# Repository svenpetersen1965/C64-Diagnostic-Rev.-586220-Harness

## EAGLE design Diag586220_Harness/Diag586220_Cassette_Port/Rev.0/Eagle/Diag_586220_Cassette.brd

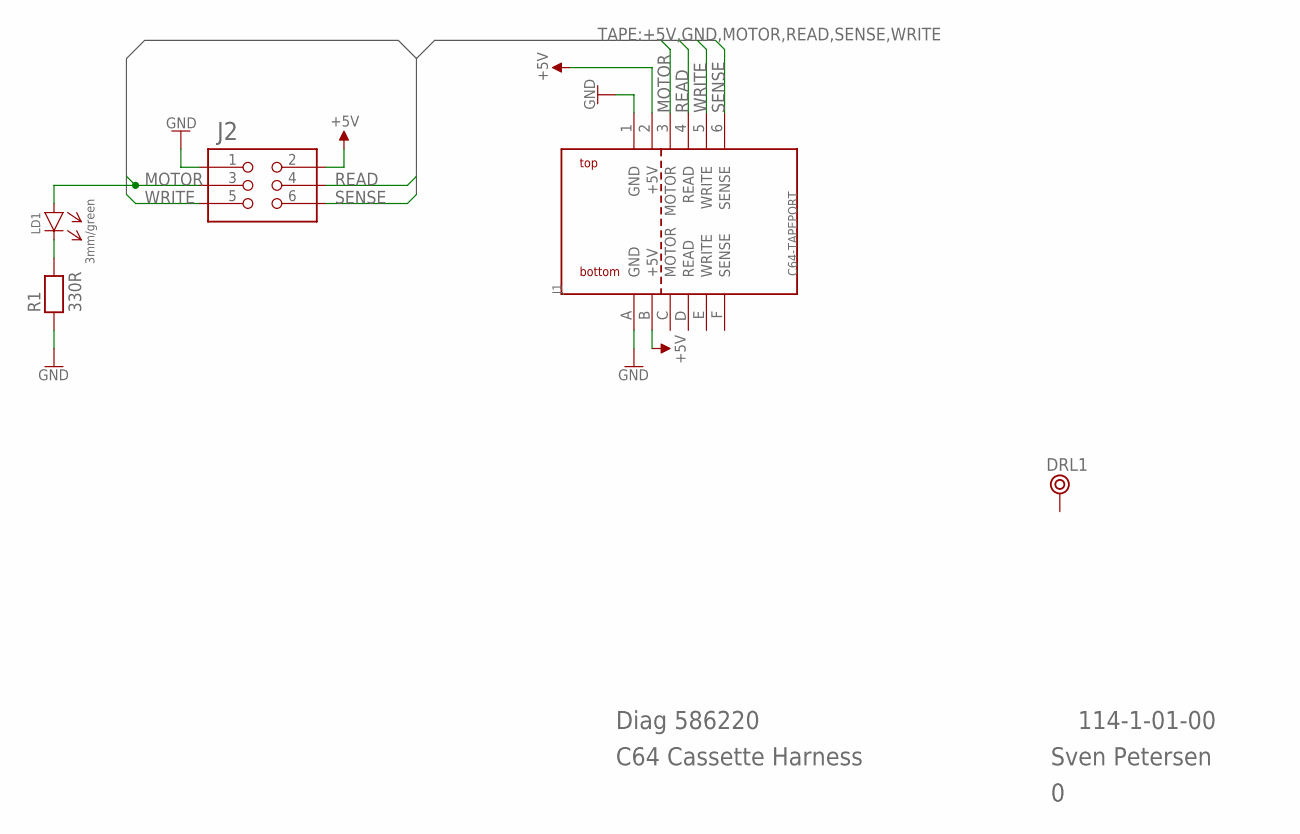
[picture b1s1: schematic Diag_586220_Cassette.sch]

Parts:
DRL1: BOHR3,5
J1: C64-TAPEPORT; TAPEPORT
J2: 2X03WV
LD1: 3mm/green; 3MM
R1: 330R; RS-2,5

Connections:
+5V: J1.2 (+5V), J1.B (+5V), J2.2
GND: J1.1 (GND), J1.A (GND), J2.1, R1.1
MOTOR: J1.3 (MOTOR), J2.3, LD1.A
unnamed: LD1.C (K), R1.2
READ: J1.4 (READ), J2.4
SENSE: J1.6 (SENSE), J2.6
WRITE: J1.5 (WRITE), J2.5

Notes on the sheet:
Diag 586220
C64 Cassette Harness
Sven Petersen
114-1-01-00

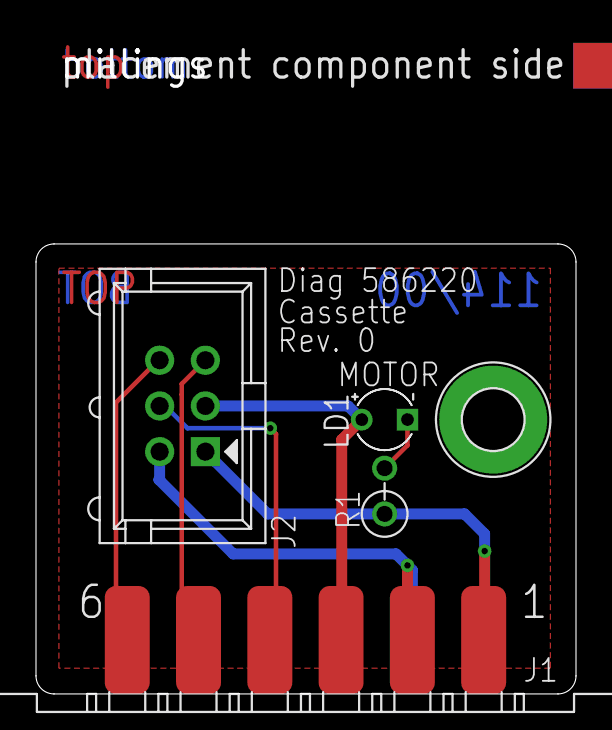
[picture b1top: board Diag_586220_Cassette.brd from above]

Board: 2 copper layers, 30.0 x 25.0 mm, 7 parts (0 on the bottom side), 7 nets.

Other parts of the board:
U$5: PCB-TITLE/
U$6: 2LAYER

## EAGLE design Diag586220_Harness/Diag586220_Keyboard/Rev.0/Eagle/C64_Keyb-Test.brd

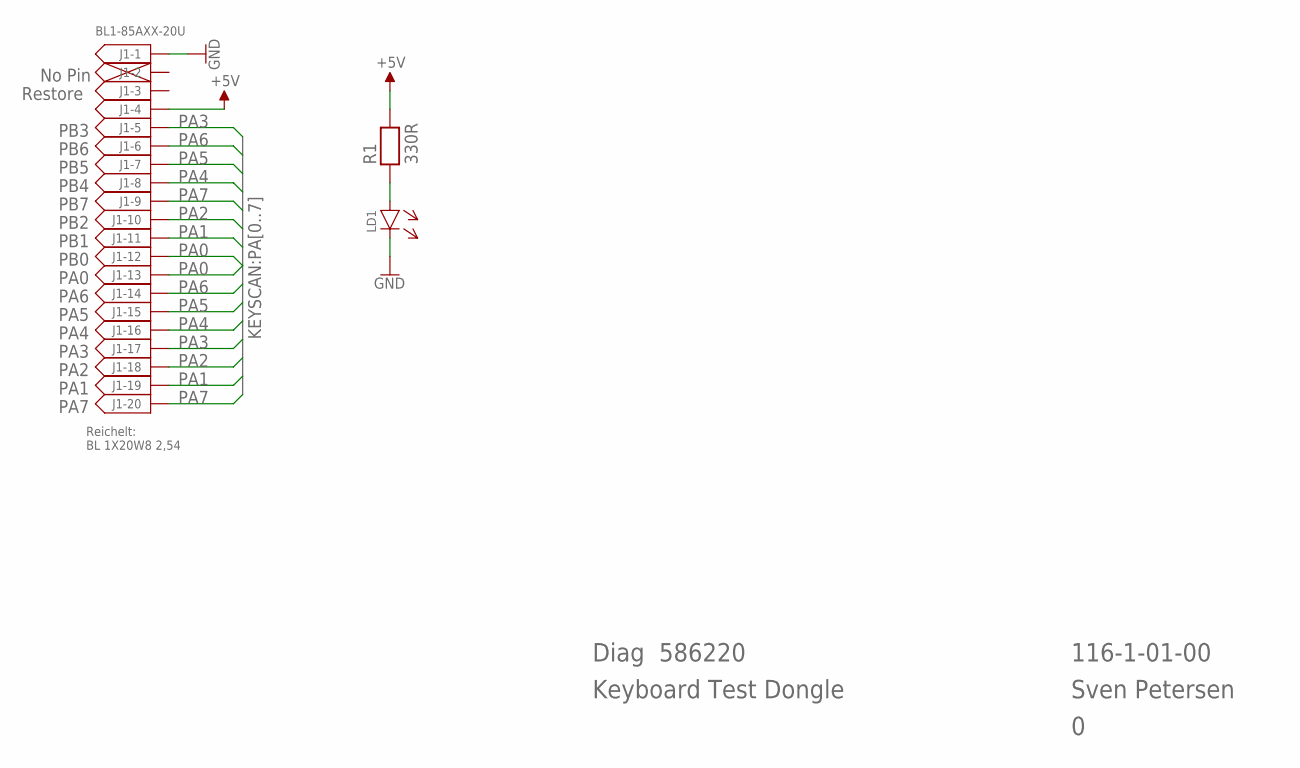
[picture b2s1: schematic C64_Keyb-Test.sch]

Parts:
J1: BL1-85AXX-20U
LD1: 3MM
R1: 330R; R-10

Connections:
+5V: J1.4, R1.2
GND: J1.1, LD1.C (K)
unnamed: LD1.A, R1.1
PA0: J1.12, J1.13
PA1: J1.11, J1.19
PA2: J1.10, J1.18
PA3: J1.5, J1.17
PA4: J1.8, J1.16
PA5: J1.7, J1.15
PA6: J1.6, J1.14
PA7: J1.9, J1.20

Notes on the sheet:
PB3
PB6
PB5
PB4
PB7
PB2
PB1
PB0
PA0
PA6
PA5
PA4
PA3
PA2
PA1
PA7
No Pin
Restore
Diag 586220
Keyboard Test Dongle
116-1-01-00
Sven Petersen
Reichelt: BL 1X20W8 2,54

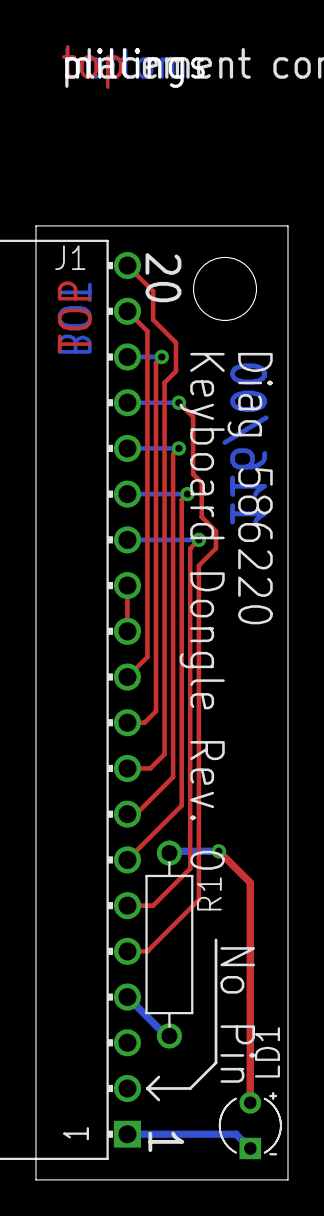
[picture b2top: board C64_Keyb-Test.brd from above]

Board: 2 copper layers, 14.0 x 53.0 mm, 5 parts (0 on the bottom side), 11 nets.

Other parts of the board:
U$6: 2LAYER
U$7: PCB-TITLE/

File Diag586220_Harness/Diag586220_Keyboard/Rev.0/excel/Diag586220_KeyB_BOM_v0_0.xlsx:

Diagnostic Rev. 586220 Harness - Keyboard Dongle Rev. 0
Bill of Material Rev. 0.0
Pos. | Qty | Value | Footprint | Ref.-No. | Comment
1 | 1 | 116-2-01-00 | 2 Layer | PCB Rev. 0 | 2 layer, Cu 35µ, HASL, 53.0mm x 14.0mm, 1.6mm FR4
2 | 1 | BL1-85AXX-20U | BL1-85AXX-20U | J1 | e.g. MPE Garry, Reichelt BL 1x20W8 2,54
3 | 1 | 3mm/green | 3MM | LD1 | LED
4 | 1 | 330R | R-10 | R1 | 1/4 Watt, 5%

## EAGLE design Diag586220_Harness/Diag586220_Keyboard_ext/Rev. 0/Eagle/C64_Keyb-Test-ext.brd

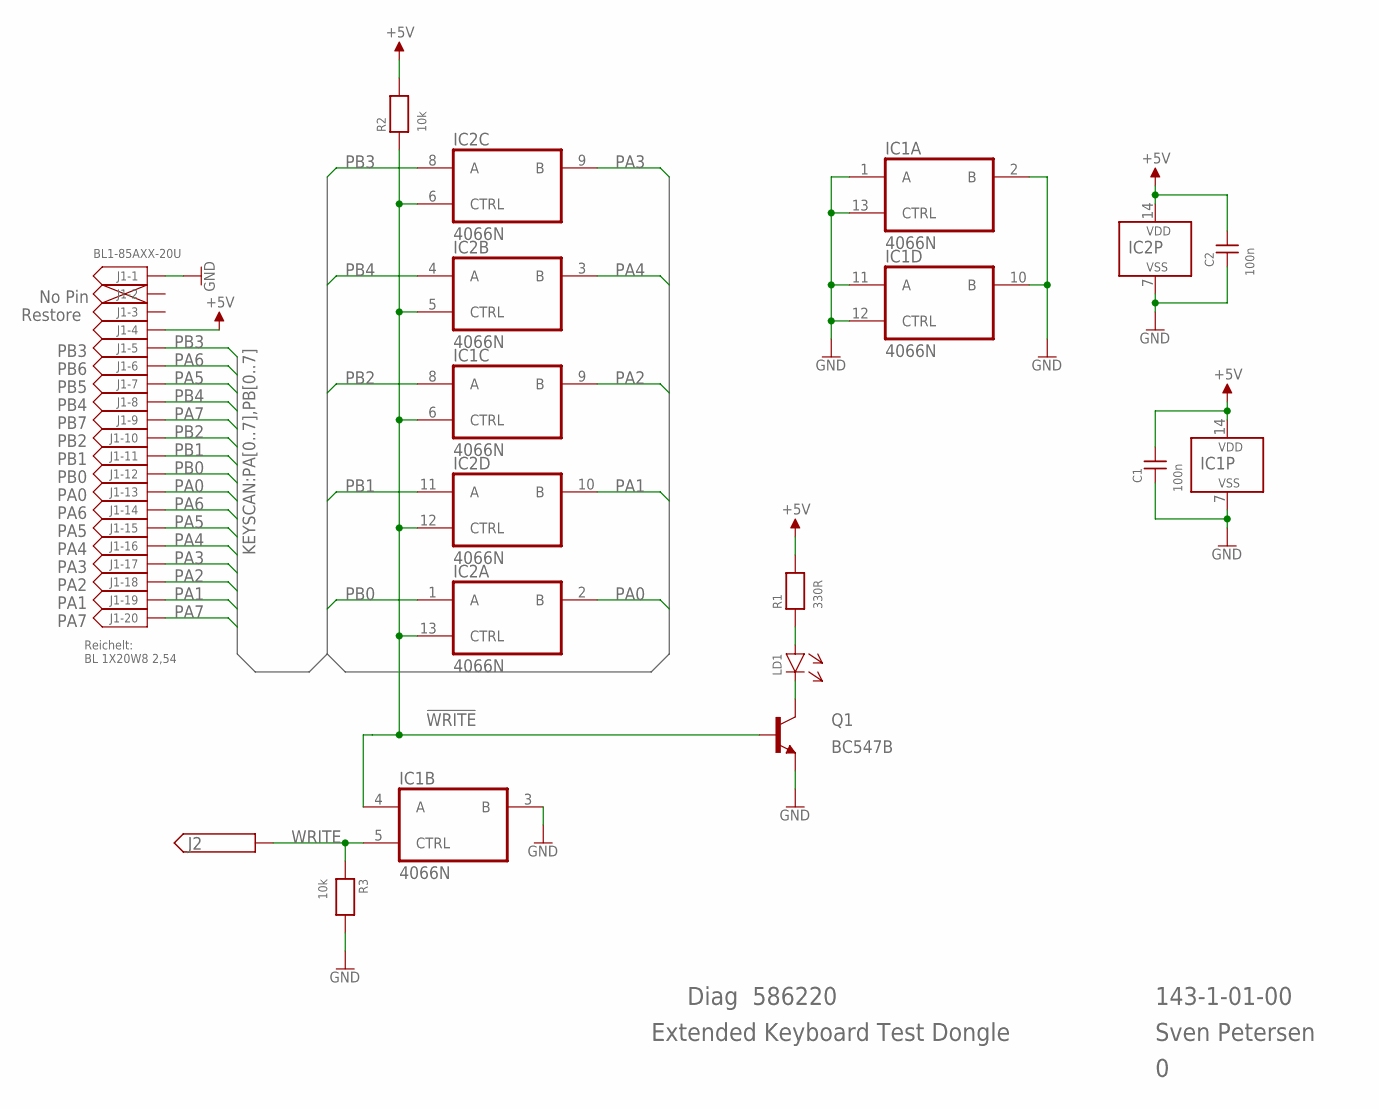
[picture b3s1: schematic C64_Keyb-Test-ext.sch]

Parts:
C1, C2: 100n; C-5
IC1, IC2: 4066N; DIL14
J1: BL1-85AXX-20U
J2: PINHD-1X1; 1X01
LD1: 3MM
Q1: BC547B; TO92
R1: 330R; R-10
R2, R3: 10k; R-10

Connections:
!WRITE: IC1.4 (A), IC1.6 (CTRL), IC2.5 (CTRL), IC2.6 (CTRL), IC2.12 (CTRL), IC2.13 (CTRL), Q1.2 (B), R2.1
+5V: C1.2, C2.2, IC1.14 (VDD), IC2.14 (VDD), J1.4, R1.2, R2.2
GND: C1.1, C2.1, IC1.1 (A), IC1.2 (B), IC1.3 (B), IC1.7 (VSS), IC1.10 (B), IC1.11 (A), IC1.12 (CTRL), IC1.13 (CTRL), IC2.7 (VSS), J1.1, Q1.1 (E), R3.2
unnamed: LD1.A, R1.1
unnamed: LD1.C (K), Q1.3 (C)
PA0: IC2.2 (B), J1.13
PA1: IC2.10 (B), J1.19
PA2: IC1.9 (B), J1.18
PA3: IC2.9 (B), J1.17
PA4: IC2.3 (B), J1.16
PA5: J1.7, J1.15
PA6: J1.6, J1.14
PA7: J1.9, J1.20
PB0: IC2.1 (A), J1.12
PB1: IC2.11 (A), J1.11
PB2: IC1.8 (A), J1.10
PB3: IC2.8 (A), J1.5
PB4: IC2.4 (A), J1.8
WRITE: IC1.5 (CTRL), J2.1, R3.1

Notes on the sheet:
PB3
PB6
PB5
PB4
PB7
PB2
PB1
PB0
PA0
PA6
PA5
PA4
PA3
PA2
PA1
PA7
No Pin
Restore
Diag 586220
Extended Keyboard Test Dongle
143-1-01-00
Sven Petersen
Reichelt: BL 1X20W8 2,54

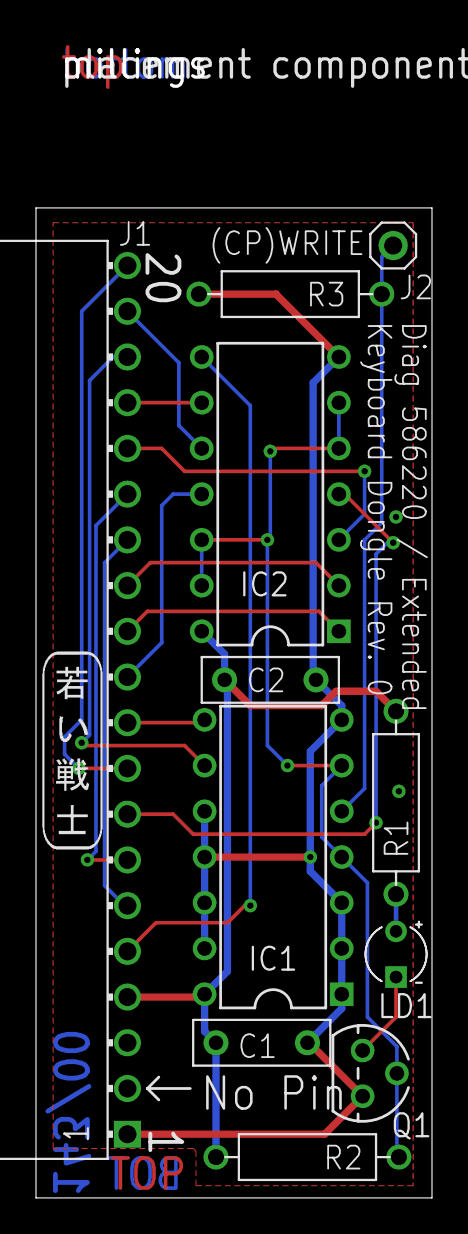
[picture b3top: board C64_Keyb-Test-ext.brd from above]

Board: 2 copper layers, 22.0 x 55.0 mm, 14 parts (0 on the bottom side), 19 nets.

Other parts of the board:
U$6: 2LAYER
U$7: PCB-TITLE/
U$17: SVEN_TAG

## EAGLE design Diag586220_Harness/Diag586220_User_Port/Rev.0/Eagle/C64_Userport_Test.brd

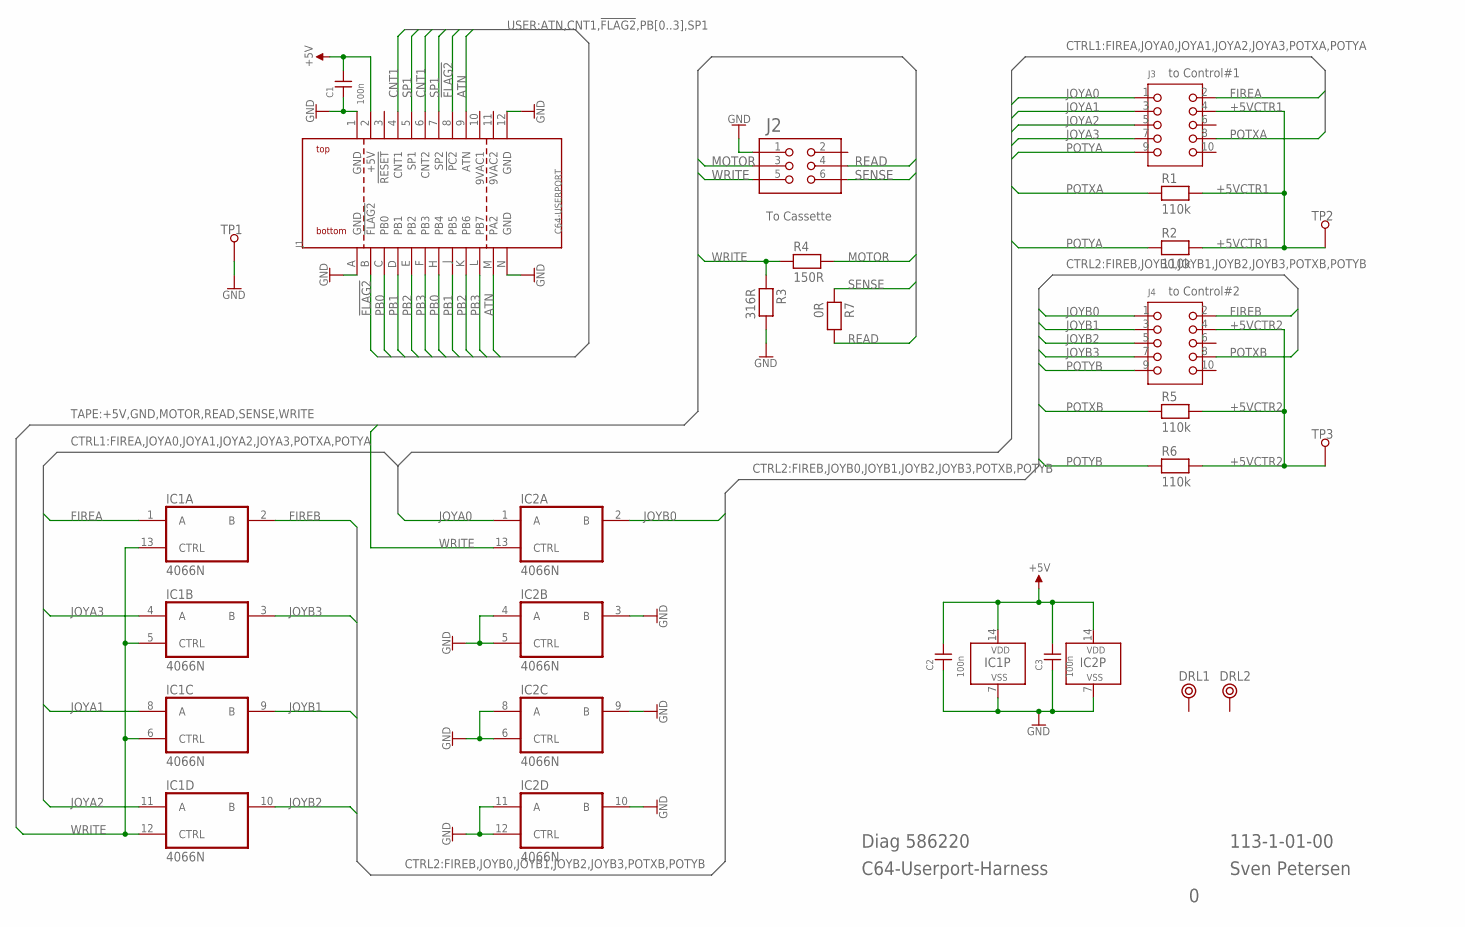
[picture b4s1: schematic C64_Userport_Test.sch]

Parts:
C1, C2, C3: 100n; C-2,5
DRL1, DRL2: BOHR3,2
IC1, IC2: 4066N; DIL14
J1: C64-USERPORT; USERPORT
J2: 2X03WV
J3, J4: 2X05WV
R1, R2, R5, R6: 110k; R-10
R3: 316R; R-10
R4: 150R; R-10
R7: 0R; R-10
TP1, TP2, TP3: L1,2_R; 1,2MM_R

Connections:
9VAC1: J1.10 (9VAC1)
9VAC2: J1.11 (9VAC2)
!FLAG2: J1.8 (!PC2), J1.B (!FLAG2)
+5V: C1.2, C2.2, C3.2, IC1.14 (VDD), IC2.14 (VDD), J1.2 (+5V)
+5VCTR1: J3.4, R1.2, R2.2, TP2.1
+5VCTR2: J4.4, R5.2, R6.2, TP3.1
ATN: J1.9 (ATN), J1.M (PA2)
CNT1: J1.4 (CNT1), J1.6 (CNT2)
FIREA: IC1.1 (A), J3.2
FIREB: IC1.2 (B), J4.2
GND: C1.1, C2.1, C3.1, IC1.7 (VSS), IC2.3 (B), IC2.4 (A), IC2.5 (CTRL), IC2.6 (CTRL), IC2.7 (VSS), IC2.8 (A), IC2.9 (B), IC2.10 (B), IC2.11 (A), IC2.12 (CTRL), J1.1 (GND), J1.12 (GND), J1.A (GND), J1.N (GND), J2.1, R3.2, TP1.1
JOYA0: IC2.1 (A), J3.1
JOYA1: IC1.8 (A), J3.3
JOYA2: IC1.11 (A), J3.5
JOYA3: IC1.4 (A), J3.7
JOYB0: IC2.2 (B), J4.1
JOYB1: IC1.9 (B), J4.3
JOYB2: IC1.10 (B), J4.5
JOYB3: IC1.3 (B), J4.7
MOTOR: J2.3, R4.2
PB0: J1.C (PB0), J1.H (PB4)
PB1: J1.D (PB1), J1.J (PB5)
PB2: J1.E (PB2), J1.K (PB6)
PB3: J1.F (PB3), J1.L (PB7)
POTXA: J3.8, R1.1
POTXB: J4.8, R5.1
POTYA: J3.9, R2.1
POTYB: J4.9, R6.1
READ: J2.4, R7.2
SENSE: J2.6, R7.1
SP1: J1.5 (SP1), J1.7 (SP2)
WRITE: IC1.5 (CTRL), IC1.6 (CTRL), IC1.12 (CTRL), IC1.13 (CTRL), IC2.13 (CTRL), J2.5, R3.1, R4.1

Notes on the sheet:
Diag 586220
C64-Userport-Harness
Sven Petersen
To Cassette
to Control#1
to Control#2
113-1-01-00

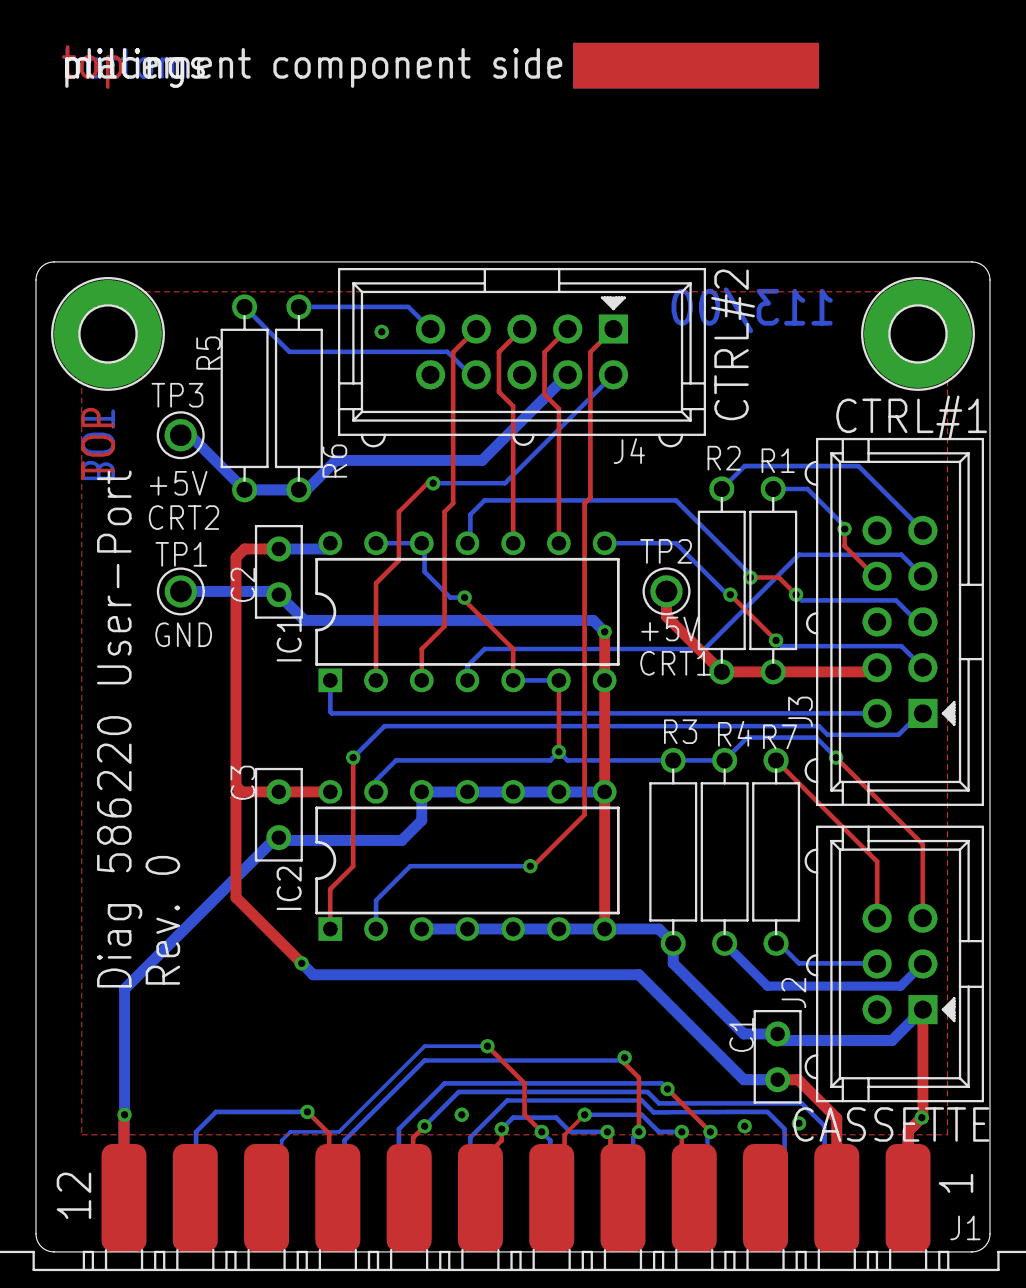
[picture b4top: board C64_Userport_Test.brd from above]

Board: 2 copper layers, 53.0 x 55.0 mm, 23 parts (0 on the bottom side), 30 nets.

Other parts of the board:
U$17: 2LAYER
U$18: PCB-TITLE/

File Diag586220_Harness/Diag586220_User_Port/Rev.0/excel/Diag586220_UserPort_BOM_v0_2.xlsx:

Diagnostic Rev. 586220 Harness - User Port Rev. 0
Bill of Material Rev. 0.2
Pos. | Qty | Value | Footprint | Ref.-No. | Comment
1 | 1 | 113-2-01-00 | 2 Layer | PCB Rev. 0 | 2 layer, Cu 35µ, HASL, LLL x BBB, 1.6mm FR4
2 | 1 | 2x3 box connector | 2X03WV | J2 | e.g. Reichelt WSL 6G
3 | 2 | 2x5 box connector | 2X05WV | J3, J4 | e.g. Reichelt WSL 10G
4 | 1 | 0R | R-10 | R7 | 0 Ohm bridge
5 | 3 | 100n/50V | C-2,5 | C1, C2, C3 | cer. cap, 2.5mm pitch
6 | 4 | 110k | R-10 | R1, R2, R5, R6 | 1/4W, 1%
7 | 1 | 150R | R-10 | R4 | 1/4W, 5%
8 | 1 | 316R | R-10 | R3 | 1/4W, 5% (316W works, 330W should work as well)
9 | 2 | HCF4066B | DIL14 | IC1, IC2 | ST Micro or equivalent
10 | 2 | DIL 14 | DIL14 | (IC1), (IC2) | DIL IC sockets
11 | 1 | 2x12, 3.96mm pitch | USERPORT | J1 | edge connector, C64 user port
12 | 3 | TP 1pin | 1,2MM_R | TP1, TP2, TP3 | Pin Header, e.g. Reichelt RND 205-00622
13 | 127cm | 10p/AWG28/1,27mm |  | Doc-No. 113-3-02-00 & Doc.-No. 113-2-01-00 | Ribbon Cable
14 | 2 | 6p IDC receptable, 2,54mm |  | Doc.-No. 113-2-01-00 | e.g. Reichelt RND 205-00680
15 | 2 | 10p IDC receptable, 2,54mm |  | Doc.-No. 113-2-02-00 | e.g. Reichelt RND 205-00682
16 | 2 | 9p D-SUB (female), IDC |  | Doc.-No. 113-2-02-00 | e.g. Reichelt D-SUB BU 09FB
17 | 1 | DIN-plug 6p |  | Doc.-No. 113-2-03-00 | e.g. Reichelt MAS 60
18 | 4cm | Wire 0,25mm², red |  | Doc.-No. 113-2-03-00 | wire, color what ever
 |  | Rev. 0.1 ® 0.2
Pos | 6 | now 110k
 | 8 | now 316R
